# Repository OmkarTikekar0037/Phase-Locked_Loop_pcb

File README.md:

# Discrete Phase-Locked Loop (PLL) on PCB

This project implements a **fully discrete Phase-Locked Loop (PLL)** using standard logic ICs, analog components, and a voltage-controlled oscillator on a custom PCB. The goal is to bridge theoretical understanding of PLLs with practical hardware realization by designing, building, and analyzing a complete feedback synchronization system.

---

## 🔷 Overview

The PLL is designed to:

* Lock onto an external reference signal (100 Hz – 10 kHz range)
* Perform **frequency multiplication** (×2, ×4, ×8 configurable)
* Demonstrate **lock acquisition (capture)** and **tracking (lock range)** behavior
* Provide observable internal signals for analysis (UP, DOWN, Vctrl, VCO output)

This implementation emphasizes **control system behavior**, **nonlinear dynamics**, and **real-world circuit constraints**.

---

## 🔷 System Architecture

The PLL is composed of the following functional blocks:

1. **Phase Frequency Detector (PFD)**

   * Built using dual D flip-flops and NAND logic
   * Generates UP/DOWN signals based on phase and frequency difference

2. **Charge Pump**

   * Converts digital UP/DOWN pulses into current pulses
   * Controls charging/discharging of the loop filter

3. **Loop Filter (RC Network)**

   * Integrates charge pump output into a smooth control voltage (Vctrl)
   * Defines loop dynamics (bandwidth, damping, stability)

4. **Voltage Controlled Oscillator (VCO)**

   * Implemented using a 555 timer in voltage-controlled mode
   * Output frequency varies with Vctrl

5. **Frequency Divider**

   * Digital counter used to scale down VCO output
   * Enables frequency multiplication in closed loop

---

## 🔷 Key Design Features

* **Second-order PLL design** with tunable damping factor (ζ ≈ 0.7)
* Adjustable loop parameters (R, C, charge pump current)
* Modular block-based design for easy debugging and testing
* Dedicated test points for internal signal observation
* Separation of analog and digital sections for noise reduction

---

## 🔷 Learning Objectives

This project demonstrates:

* Practical implementation of **feedback control systems**

* Relationship between **phase, frequency, and time-domain behavior**

* Design trade-offs between:

  * Stability vs speed
  * Capture range vs noise
  * Loop gain vs oscillation

* Real-world non-idealities:

  * Charge pump mismatch
  * Loop filter noise sensitivity
  * VCO nonlinearity

---

## 🔷 Observations & Experiments

The setup allows direct observation of:

* Lock acquisition process (capture range behavior)
* Stable locked state (minimal phase error)
* Effect of loop filter parameters on system response
* Impact of VCO gain and charge pump current on stability

---

## 🔷 Applications

While implemented as a low-frequency prototype, the same principles apply to:

* Microcontroller clock generation
* RF frequency synthesizers
* Motor synchronization systems
* Communication systems (clock/data recovery)

---

## 🔷 Project Significance

This project serves as a **hardware-level exploration of PLLs**, transforming abstract concepts into measurable electrical behavior. It provides a strong foundation for advanced topics such as:

* High-frequency PLL design
* Digital PLLs (FPGA-based)
* Control system modeling and stability analysis

---

## 🔷 Status

🚧 In development — includes schematic design, PCB layout, and experimental validation.

---

## 🔷 Author

Omkar Tikekar
Electronics & Telecommunication Engineering

---

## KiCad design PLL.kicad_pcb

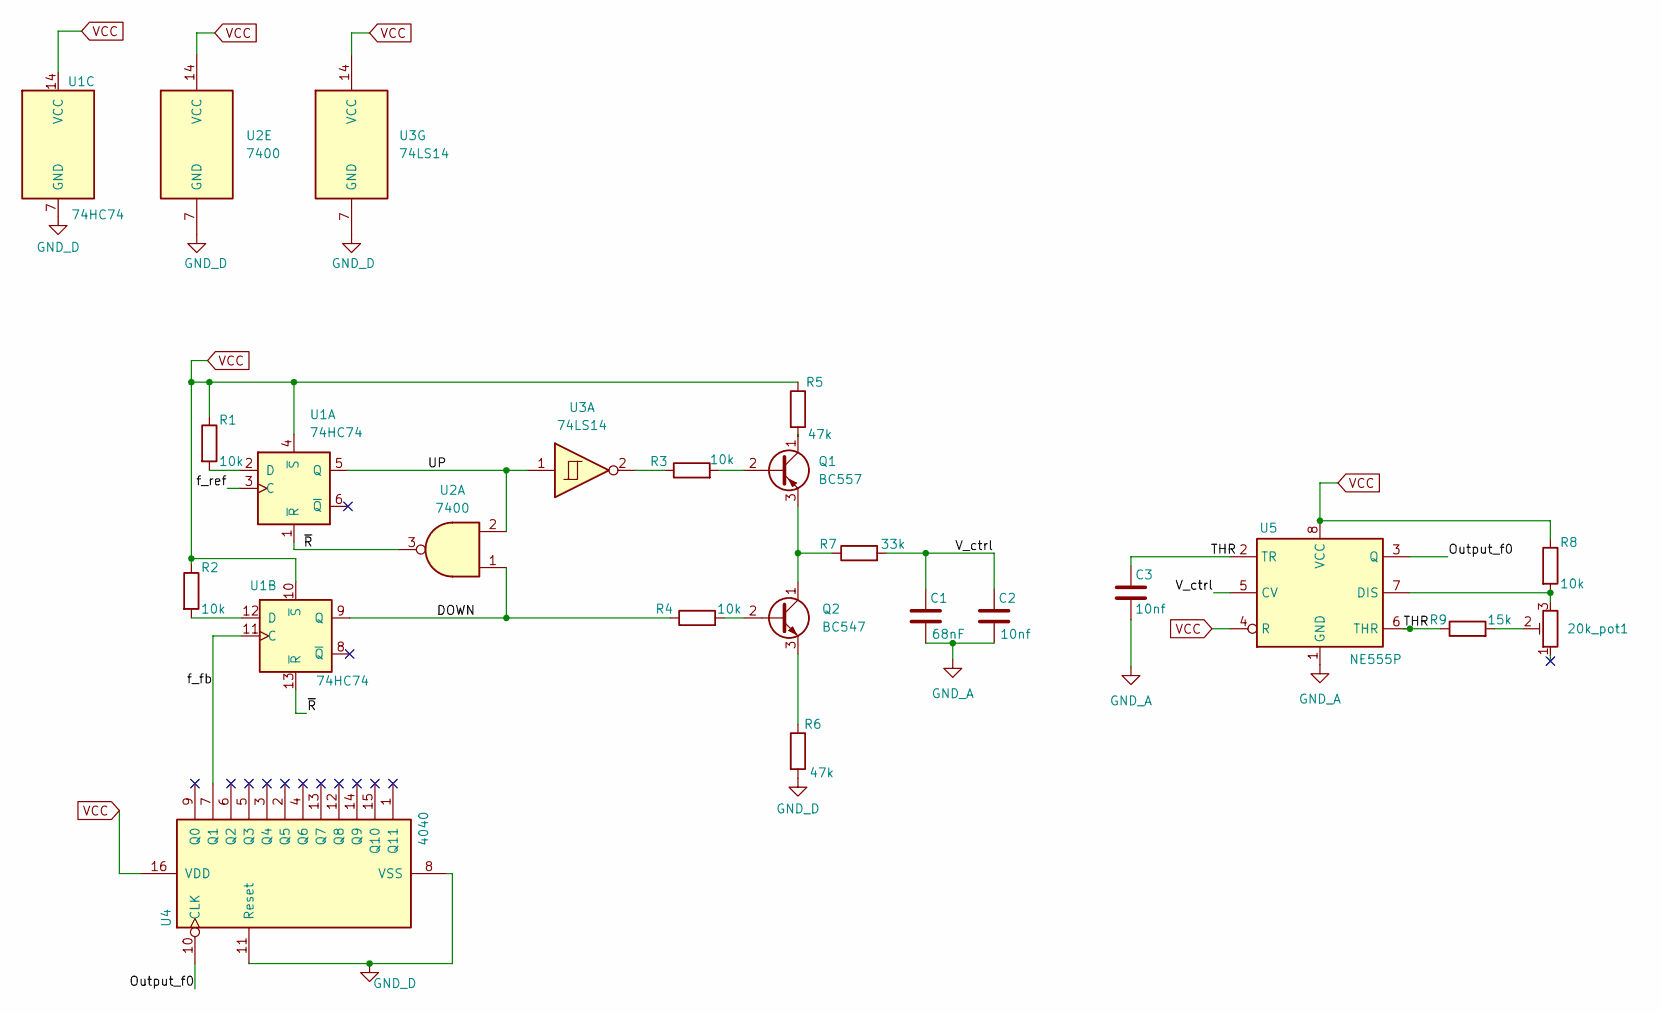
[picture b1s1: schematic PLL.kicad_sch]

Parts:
20k_pot1: R_Potentiometer_Trim; Potentiometer_Runtron_RM-063_Horizontal
C1: 68nF; C_Disc_D3.0mm_W1.6mm_P2.50mm
C2, C3: 10nf; C_Disc_D3.0mm_W1.6mm_P2.50mm
Q1: BC557; TO-92_Inline
Q2: BC547; TO-92_Inline
R1, R2, R3, R4, R8: 10k; R_Axial_DIN0207_L6.3mm_D2.5mm_P7.62mm_Horizontal
R5, R6: 47k; R_Axial_DIN0207_L6.3mm_D2.5mm_P7.62mm_Horizontal
R7: 33k; R_Axial_DIN0207_L6.3mm_D2.5mm_P7.62mm_Horizontal
R9: 15k; R_Axial_DIN0207_L6.3mm_D2.5mm_P7.62mm_Horizontal
U1: 74HC74; DIP-14_W7.62mm
U2: 7400; DIP-14_W7.62mm
U3: 74LS14
U4: 4040; DIP-16_W7.62mm
U5: NE555P; DIP-8_W7.62mm

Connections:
/DOWN: R4.1, U1.9 (Q), U2.1
/Output_f0: U4.10 (CLK), U5.3 (Q)
/THR: C3.1, R9.1, U5.2 (TR), U5.6 (THR)
/UP: U1.5 (Q), U2.2, U3.1
/V_ctrl: C1.1, C2.1, R7.2, U5.5 (CV)
/f_fb: U1.11 (C), U4.7 (Q1)
/f_ref: U1.3 (C)
/~R: U1.1 (~R), U1.13 (~R), U2.3
GND_A: C1.2, C2.2, C3.2, U5.1 (GND)
GND_D: R6.2, U1.7 (GND), U2.7 (GND), U3.7 (GND), U4.8 (VSS), U4.11 (Reset)
unnamed: 20k_pot1.2, R9.2
unnamed: Q1.2 (B), R3.2
unnamed: Q1.1 (C), R5.2
unnamed: Q1.3 (E), Q2.1 (C), R7.1
unnamed: Q2.2 (B), R4.2
unnamed: Q2.3 (E), R6.1
unnamed: R3.1, U3.2
unnamed: R1.2, U1.2 (D)
unnamed: R2.2, U1.12 (D)
unnamed: 20k_pot1.3, R8.2, U5.7 (DIS)
VCC: R1.1, R2.1, R5.1, R8.1, U1.4 (~S), U1.10 (~S), U1.14 (VCC), U2.14 (VCC), U3.14 (VCC), U4.16 (VDD), U5.4 (R), U5.8 (VCC)

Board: 2 copper layers, 19 parts (0 on the bottom side), 19 nets, no tracks yet.

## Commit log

2026-04-15 initial empty commit
2026-04-15 Phase detector completed
2026-04-15 Revise README to enhance project documentation
    Expanded project description and added sections on system architecture, key design features, learning objectives, observations, applications, and project significance.
2026-04-15 corrected Phase detector
2026-04-15 BJT push-pull charge pump added
2026-04-16 Added Low-Pass Filter and footprints for resistors
2026-04-16 555 Timer Voltage controlled oscillator circuitry added
2026-04-16 Divide by 4 counter added
